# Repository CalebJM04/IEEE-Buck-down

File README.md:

# IEEE Buck down
Buck down (12VDC-5VDC) for IEEE 2026 robot

This was designed for the usage of three servos on the robot, hence the three outputs.

Schematic

The schematic is very simple and straightforward. It was designed in accordance with the TPS561208DDCR datasheet and TI Webbench Power Designer.

 PCB

The PCB is also very straightforward. The board is two layers, with a ground pour on the bottom-most layer. The top layer is where all signal/power routing is done. The board features three outputs at the bottom. These outputs are 2.54mm THT holes, designed for soldering with simple jumper cables.

Final PCB

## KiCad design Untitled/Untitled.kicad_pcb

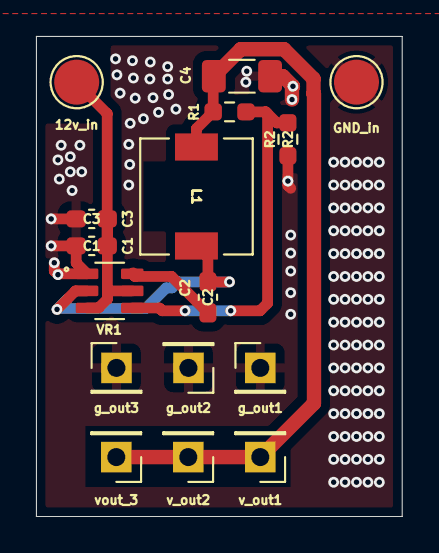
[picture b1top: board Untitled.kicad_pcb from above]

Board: 2 copper layers, 20.3 x 26.7 mm, 16 parts (0 on the bottom side), 6 nets.

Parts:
12v_in: 12v_in; TestPoint_Pad_D2.5mm
C1, C3: 10uF; C_0603_1608Metric_Pad1.08x0.95mm_HandSolder
C2: 100nf; C_0603_1608Metric_Pad1.08x0.95mm_HandSolder
C4: 47uF; C_1206_3216Metric_Pad1.33x1.80mm_HandSolder
GND_in: GND_in; TestPoint_Pad_D2.5mm
L1: 4.7uH; IND_EPCOS_B82462A4_EPC
R1: 56.2k; R_0603_1608Metric_Pad0.98x0.95mm_HandSolder
R2: 10k; R_0603_1608Metric_Pad0.98x0.95mm_HandSolder
VR1: TPS561208DDCR; SOT95P280X110-6N
g_out1: g_out1; PinHeader_1x01_P2.54mm_Vertical
g_out2: g_out2; PinHeader_1x01_P2.54mm_Vertical
g_out3: g_out3; PinHeader_1x01_P2.54mm_Vertical
v_out1: vout_1; PinHeader_1x01_P2.54mm_Vertical
v_out2: vout_2; PinHeader_1x01_P2.54mm_Vertical
vout_3: vout_3; PinHeader_1x01_P2.54mm_Vertical

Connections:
+5V: C4.2, L1.1, R1.1, v_out1.1, v_out2.1, vout_3.1
+12V: 12v_in.1, C1.1, C3.1, VR1.3 (VIN), VR1.5 (EN)
GND: C1.2, C3.2, C4.1, GND_in.1, R2.2, VR1.1 (GND), g_out1.1, g_out2.1, g_out3.1
unnamed: C2.2, L1.2, VR1.2 (SW)
unnamed: C2.1, VR1.6 (VBST)
unnamed: R1.2, R2.1, VR1.4 (VFB)

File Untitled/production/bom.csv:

Designator,Footprint,Quantity,Value,LCSC Part #
12V_IN,TestPoint_Pad_D2.5mm,1,12v_in,
"C1, C3",0603,2,10uF,
C2,0603,1,100nf,
C4,1206,1,47uF,
GND_IN,TestPoint_Pad_D2.5mm,1,GND_in,
G_OUT1,PinHeader_1x01_P2.54mm_Vertical,1,g_out1,
G_OUT2,PinHeader_1x01_P2.54mm_Vertical,1,g_out2,
G_OUT3,PinHeader_1x01_P2.54mm_Vertical,1,g_out3,
L1,IND_EPCOS_B82462A4_EPC,1,4.7uH,
R1,0603,1,56.2k,
R2,0603,1,10k,
VOUT_3,PinHeader_1x01_P2.54mm_Vertical,1,vout_3,
VR1,SOT95P280X110-6N,1,TPS561208DDCR,
V_OUT1,PinHeader_1x01_P2.54mm_Vertical,1,vout_1,
V_OUT2,PinHeader_1x01_P2.54mm_Vertical,1,vout_2,

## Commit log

2025-10-02 finished schematic
2025-10-02 added r values
2025-10-02 created pcb and imported all footprints
2025-10-02 updated TP footprint and added names
2025-10-02 version1
    I wanna figure out how to reduce the size somehow. but this version should work fine
2025-10-02 updated c4 to 1206
2025-10-03 updated to 2.54tht pads
2025-10-03 made prod. sent to daniel
